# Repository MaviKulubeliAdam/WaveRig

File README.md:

# WaveRig

An open-hardware ESP32-S3 BLE bridge between amateur radio transceivers and [Wavelog Mobile](https://github.com/MaviKulubeliAdam/Wavelog-Mobile) / [Wavelog](https://github.com/wavelog/wavelog).

WaveRig connects to your radio's CI-V (ICOM) or CAT (Yaesu/Kenwood) interface, reads live frequency, mode and power, and streams it over Bluetooth Low Energy straight into your QSO log — no more typing frequency and mode by hand for every contact.

---

## Status: Early hardware development

- 🔧 Schematic in progress
- ⬜ PCB layout not started yet (65×45 mm, 2-layer target)
- ⬜ Firmware not started yet
- ⬜ No boards fabricated/tested yet

This repository will track schematic/PCB sources, the bill of materials, and firmware once development begins. Contributions, feedback and testing help are welcome even at this stage.

---

## Planned Features

- **CI-V support** — ICOM radios (IC-7300, IC-705, IC-9700, IC-7610, and others) via a 3.5mm jack
- **CAT support** — Yaesu / Kenwood radios (FT-891, FT-991A, FT-DX10, TS-590, TS-890, and others) via RS-232 (DB9) through a MAX202 level shifter
- **BLE GATT service** — frequency, mode, submode, TX power and rig model pushed live to any connected app
- **Rechargeable** — LiPo battery with USB-C charging (TC4056A) and protection (DW01A + FS8205A)
- **USB-C native flashing** — no external USB-serial adapter needed; flash directly over the same USB-C port
- **OLED status display** — shows frequency, mode and connection status at a glance
- **BLE OTA firmware updates** — update via the companion phone app, no cable required (planned)

## Hardware Overview

| | |
|---|---|
| MCU | ESP32-S3-WROOM-1 (N16R8, 16MB flash) |
| Power | LiPo 3.7V, USB-C charging, boost to 3.3V (MT3608) |
| CI-V | 3.5mm jack, open-drain driver (2N7000) |
| CAT / RS-232 | DB9, MAX202EESE+T level shifter |
| Display | I2C OLED (SSD1306, 4-pin connector) |
| PCB | 65×45mm, 2-layer |

Schematic and PCB design are being developed by **Süalp, TA4HCK**. Full BOM, pin assignments and net-by-net connection notes will be published in this repo as the hardware design is finalized.

## Firmware Roadmap

1. BLE GATT service (frequency / mode / submode / power / rig model, notify-based)
2. CI-V protocol parsing (ICOM)
3. CAT protocol parsing (Yaesu / Kenwood)
4. OLED UI
5. BLE OTA updates (phone acts as the bridge to the internet — no Wi-Fi needed on-device)

## Related Projects

- [Wavelog Mobile](https://github.com/MaviKulubeliAdam/Wavelog-Mobile) — the Android companion app WaveRig connects to
- [Wavelog](https://github.com/wavelog/wavelog) — the self-hosted amateur radio logging server

## Contributing

This project is in early hardware development — schematic and PCB files, along with contribution guidelines, will be added as the design stabilizes. Issues and discussion are welcome in the meantime.

## License

Licensed under the [Apache License 2.0](LICENSE).

---

By Erkin, TA4RX / SP9AQG (firmware / software) and Süalp, TA4HCK (schematic / PCB)

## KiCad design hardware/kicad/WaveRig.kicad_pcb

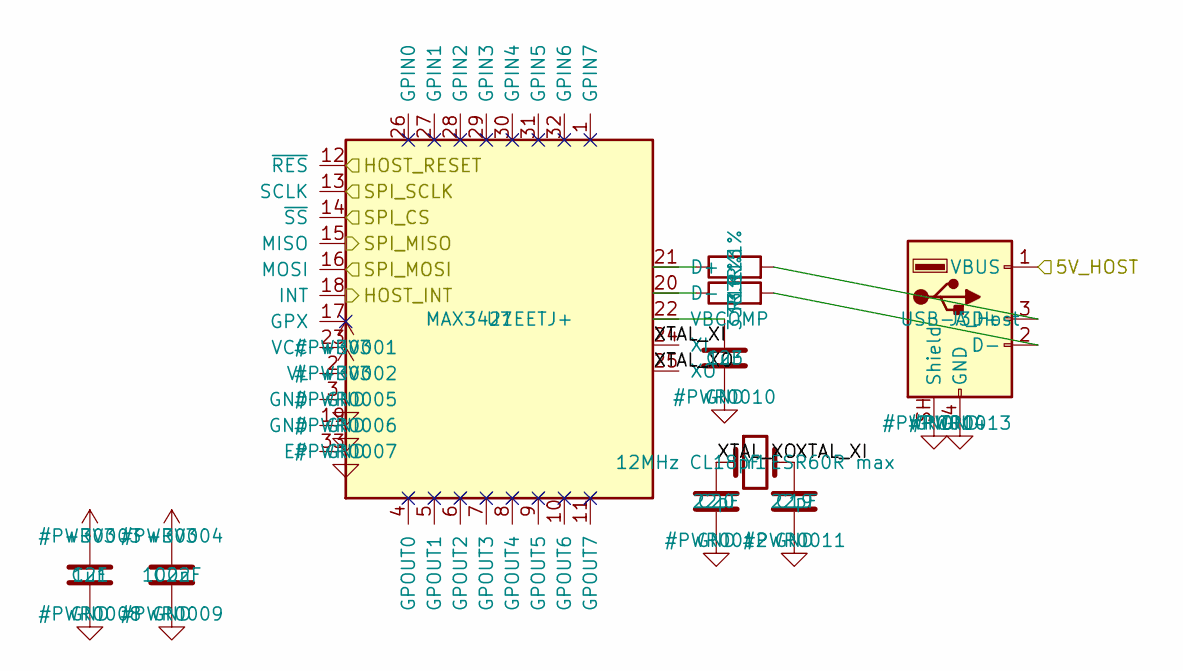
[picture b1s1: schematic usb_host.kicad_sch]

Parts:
C19, C20: 22pF; C_0603_1608Metric
C21, C23: 1uF; C_0603_1608Metric
C22: 100nF; C_0603_1608Metric
J3: USB-A_Host; USB_A_Receptacle_GCT_USB1046
R15, R16: 33R 1%; R_0603_1608Metric
U7: MAX3421EETJ+; QFN-32-1EP_5x5mm_P0.5mm_EP3.7x3.7mm
Y1: 12MHz CL18pF ESR60R max; Crystal_SMD_HC49-SD

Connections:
+3V3: C21.1, C22.1, U7.2 (VL), U7.23 (VCC); also elsewhere on the board
/HOST_INT: U7.18 (INT); also elsewhere on the board
/HOST_RESET: U7.12 (~RES); also elsewhere on the board
/SPI_CS: U7.14 (~SS); also elsewhere on the board
/SPI_MISO: U7.15 (MISO); also elsewhere on the board
/SPI_MOSI: U7.16 (MOSI); also elsewhere on the board
/SPI_SCLK: U7.13 (SCLK); also elsewhere on the board
/USB_Host/XTAL_XI: C19.1, U7.24 (XI), Y1.2
/USB_Host/XTAL_XO: C20.1, U7.25 (XO), Y1.1
unnamed: J3.3 (D+), R15.2
unnamed: J3.2 (D-), R16.2
unnamed: R15.1, U7.21 (D+)
unnamed: R16.1, U7.20 (D-)
unnamed: C23.1, U7.22 (VBCOMP)

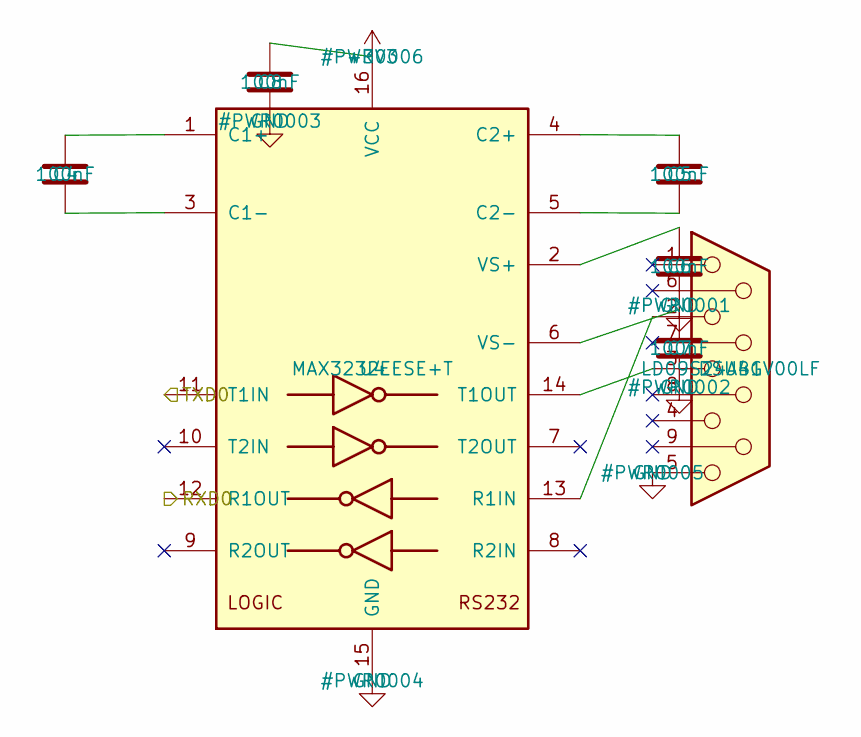
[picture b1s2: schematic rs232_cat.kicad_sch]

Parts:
C4, C5, C6, C7, C8: 100nF; C_0603_1608Metric
DSUB1: LD09S24A4GV00LF; DSUB-9_Socket_Horizontal_P2.77x2.54mm_EdgePinOffset9.40mm
U4: MAX3232EESE+T; SOIC-16_3.9x9.9mm_P1.27mm

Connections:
+3V3: C8.1, U4.16 (VCC); also elsewhere on the board
/RXD0: U4.12 (R1OUT); also elsewhere on the board
/TXD0: U4.11 (T1IN); also elsewhere on the board
unnamed: C4.1, U4.1 (C1+)
unnamed: C4.2, U4.3 (C1-)
unnamed: C5.1, U4.4 (C2+)
unnamed: C5.2, U4.5 (C2-)
unnamed: DSUB1.2, U4.13 (R1IN)
unnamed: DSUB1.3, U4.14 (T1OUT)
unnamed: C6.1, U4.2 (VS+)
unnamed: C7.1, U4.6 (VS-)

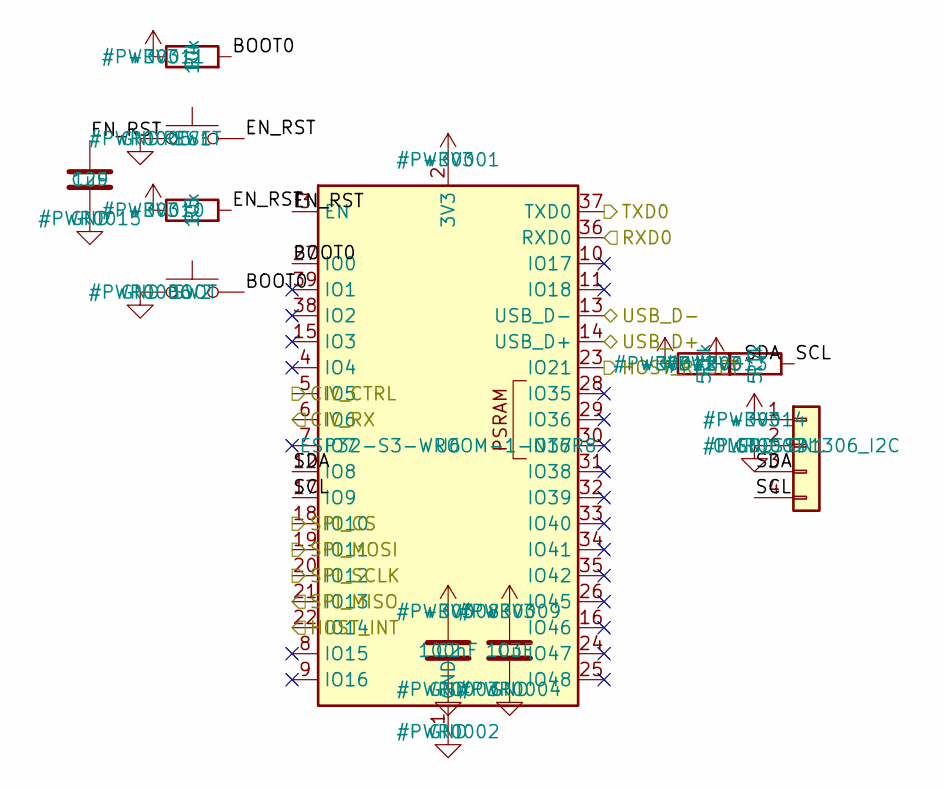
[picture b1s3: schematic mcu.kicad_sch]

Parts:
C2: 100nF; C_0603_1608Metric
C3: 10uF; C_0603_1608Metric
C29: 1uF; C_0603_1608Metric
CN1: OLED_SSD1306_I2C; JST_PH_B4B-PH-K_1x04_P2.00mm_Vertical
R4, R5: 10k; R_0603_1608Metric
R6, R7: 5.1k; R_0603_1608Metric
SW1: RESET; SW_SPST_B3S-1000
SW2: BOOT; SW_SPST_B3S-1000
U6: ESP32-S3-WROOM-1-N16R8; ESP32-S3-WROOM-1

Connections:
+3V3: C2.1, C3.1, CN1.1, R4.1, R5.1, R6.1, R7.1, U6.2 (3V3); also elsewhere on the board
/CIV_CTRL: U6.5 (IO5); also elsewhere on the board
/CIV_RX: U6.6 (IO6); also elsewhere on the board
/HOST_INT: U6.22 (IO14); also elsewhere on the board
/HOST_RESET: U6.23 (IO21); also elsewhere on the board
/MCU/BOOT0: R4.2, SW2.2, U6.27 (IO0)
/MCU/EN_RST: C29.1, R5.2, SW1.2, U6.3 (EN)
/MCU/SCL: CN1.4, R7.2, U6.17 (IO9)
/MCU/SDA: CN1.3, R6.2, U6.12 (IO8)
/RXD0: U6.36 (RXD0); also elsewhere on the board
/SPI_CS: U6.18 (IO10); also elsewhere on the board
/SPI_MISO: U6.21 (IO13); also elsewhere on the board
/SPI_MOSI: U6.19 (IO11); also elsewhere on the board
/SPI_SCLK: U6.20 (IO12); also elsewhere on the board
/TXD0: U6.37 (TXD0); also elsewhere on the board
/USB_D+: U6.14 (USB_D+); also elsewhere on the board
/USB_D-: U6.13 (USB_D-); also elsewhere on the board

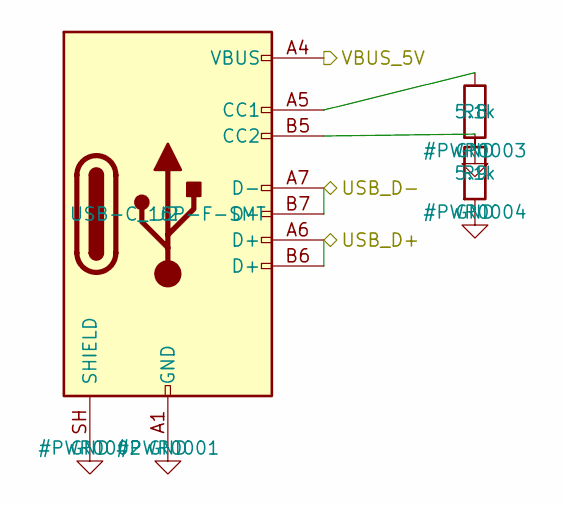
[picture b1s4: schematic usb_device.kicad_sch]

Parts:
J2: USB-C_16P-F-SMT; USB_C_Receptacle_GCT_USB4115-03-C
R8, R9: 5.1k; R_0603_1608Metric

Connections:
/USB_D+: J2.A6 (D+), J2.B6 (D+); also elsewhere on the board
/USB_D-: J2.A7 (D-), J2.B7 (D-); also elsewhere on the board
unnamed: J2.A5 (CC1), R8.1
unnamed: J2.B5 (CC2), R9.1

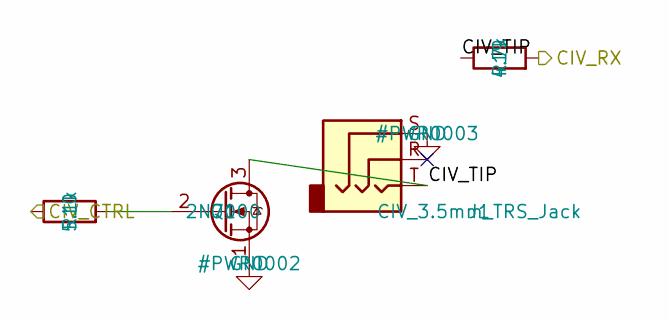
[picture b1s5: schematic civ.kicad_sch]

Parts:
J1: CIV_3.5mm_TRS_Jack; Jack_3.5mm_CUI_SJ1-3523N_Horizontal
Q1: 2N7000; TO-92_Inline
R10: 5.1k; R_0603_1608Metric
R19: 4.7k; R_0603_1608Metric

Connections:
/CIV/CIV_TIP: J1.T, Q1.3 (D), R19.1
/CIV_CTRL: R10.1; also elsewhere on the board
/CIV_RX: R19.2; also elsewhere on the board
unnamed: Q1.2 (G), R10.2

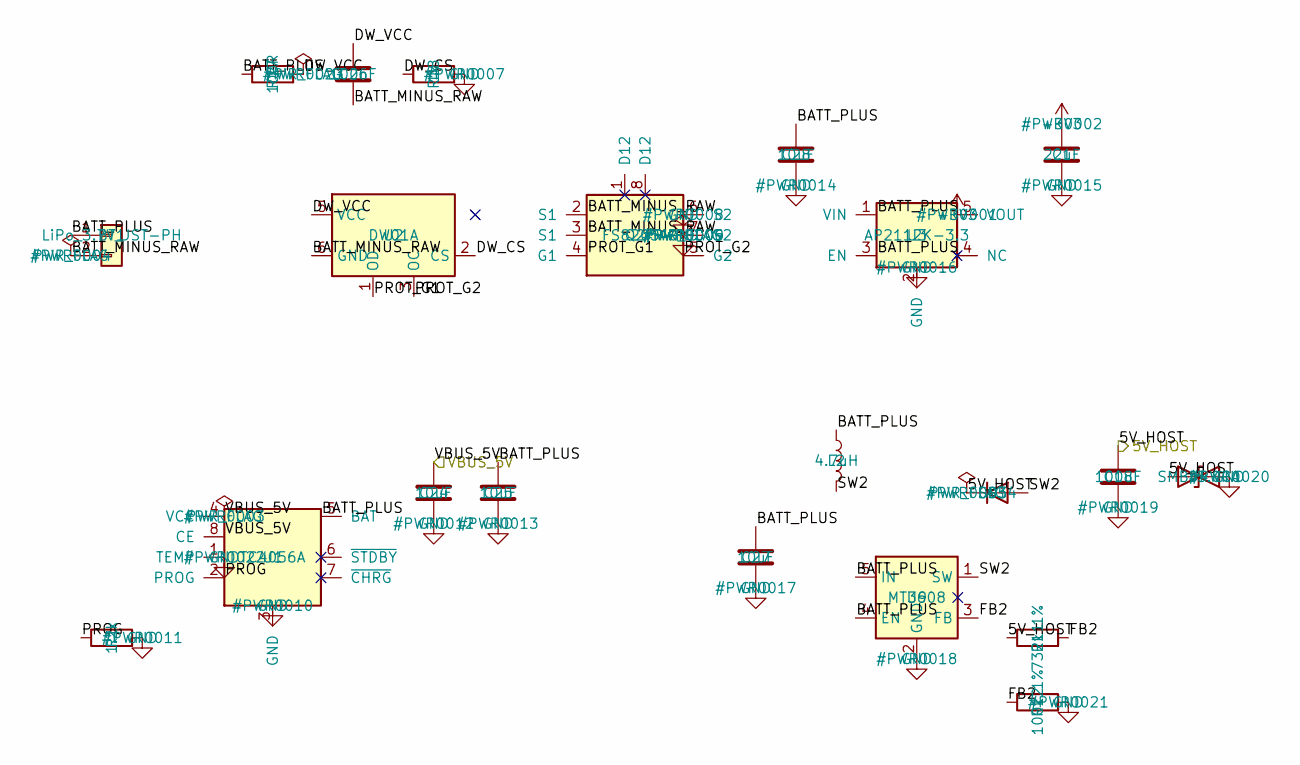
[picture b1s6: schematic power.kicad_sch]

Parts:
BT1: LiPo_3.7V_JST-PH; JST_PH_B2B-PH-K_1x02_P2.00mm_Vertical
C1: 22uF; C_0805_2012Metric
C18: 100uF; C_1206_3216Metric
C24, C25, C27, C28: 10uF; C_0805_2012Metric
C26: 100nF; C_0603_1608Metric
D3: SS34; D_SMA
D4: SMBJ5.0CA; D_SMB
L2: 4.7uH; L_6.3x6.3_H3
Q2: FS8205A; TSSOP-8_4.4x3mm_P0.65mm
R1: 1.2k; R_0603_1608Metric
R11: 732k 1%; R_0603_1608Metric
R12: 100k 1%; R_0603_1608Metric
R17: 100R; R_0603_1608Metric
R18: 1k; R_0603_1608Metric
U1: TC4056A; SOIC-8_3.9x4.9mm_P1.27mm
U2: DW01A; SOT-23-6
U3: AP2112K-3.3; SOT-23-5
U9: MT3608; SOT-23-6

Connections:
+3V3: C1.1, U3.5 (VOUT); also elsewhere on the board
/Power/BATT_PLUS: BT1.1, C25.1, C27.1, C28.1, L2.1, R17.1, U1.5 (BAT), U3.1 (VIN), U3.3 (EN), U9.4 (EN), U9.5 (IN)
/Power/DW_CS: R18.1, U2.2 (CS)
/Power/FB2: R11.2, R12.1, U9.3 (FB)
/Power/PROG: R1.1, U1.2 (PROG)
/Power/PROT_G1: Q2.4 (G1), U2.1 (OD)
/Power/PROT_G2: Q2.5 (G2), U2.3 (OC)
/Power/SW2: D3.2 (A), L2.2, U9.1 (SW)

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
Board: 2 copper layers, 56 parts (0 on the bottom side), 48 nets, no tracks yet.
